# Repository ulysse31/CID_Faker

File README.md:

# DISCLAIMER :
# THIS PROJECT IS A PATCH MADE BY MYSELF, FOR MYSELF, AND IT AIMS TO COMPENSATE, THE LACK OF BUG CORRECTIONS IN THIRD PARTY REPLACEMENT SCREENS (CHINESE ANDROID BASED SCREENS) THAT DO NOT HAVE IMPLEMENTED THIS PARTICULAR CASE ON THEIR MCU FIRMWARE...

# WARNING !!! WE ARE TALKING ABOUT INJECTING DATA TO THE CAR NETWORK, THIS IS AT YOUR OWN RISK !!! I WILL NOT BE RESPONSIBLE FOR ANY HARM YOU MAY CAUSE TO YOUR CAR, YOURSELF, OR ANY OTHER
# YOU HAVE BEEN WARNED !!!
# CID_Faker
A CID can bus simulator:

CID (Central Information Display) on BMW cars from 2004 to 2011 is the designation for the car LCD screen.
Some of those screens are connected to the can bus of the car (at least BMW flap screens).
If you try to replace this type of screen with something else (like an Android Head Unit) you'll loose the ability to 
interact with the BMW original menu (no actions from idrive interpreted).

This project supposes that this is because of the absence of the can message id from the screen : "why take into
account moves from idrive if no screen detected" ... thats what the engineer may have thought when implementing this
on the CCC controller ...

This little code will so generate fake CID id messages on the can bus of the car, to simulate the presence of the CID.
CID sends messages with id 0x33a (status) and 0x4f3 (network).
All the main job will be to find the right messages, their combinations and timings.

Project uses platformIO for easy compilation and development.

For now, I'm using a Pro Micro board 5V@16Mhz, and a well known MCP2515 CAN Controller module, more precisely the
MCP2515 CAN controller with a 8Mhz oscillator and TJA1050 CAN transceiver.

You'll find on "Hardware" folder 2 types of designs :

- USB_Powered (tested working/recommended): this light version aims to be connected to the Android HU on its USB port, allowing it to be
powered up once the Android is up (key car inserted), and powered off when Android goes off (key car taken out)

- Standalone (not tested/under construction): this version aims to be more "unrelated" the Android HU, it is up the user to find a power
cable source from the car (preferrably, a source that is NOT always on ...)

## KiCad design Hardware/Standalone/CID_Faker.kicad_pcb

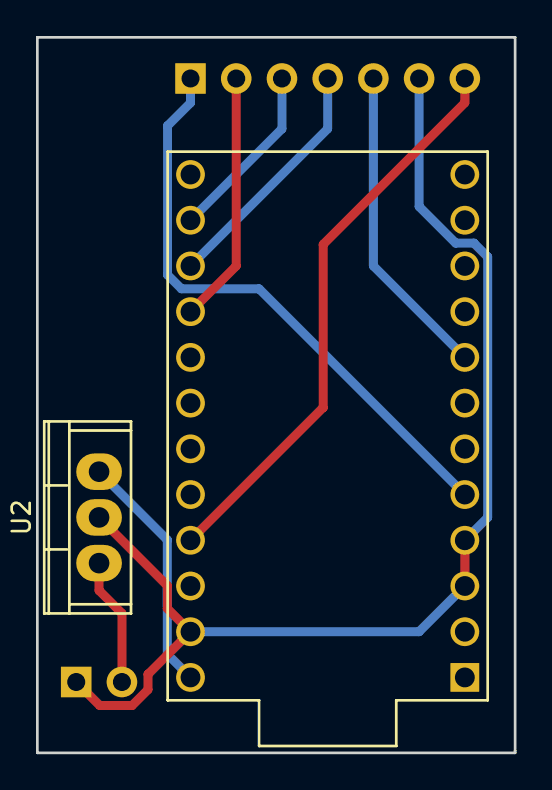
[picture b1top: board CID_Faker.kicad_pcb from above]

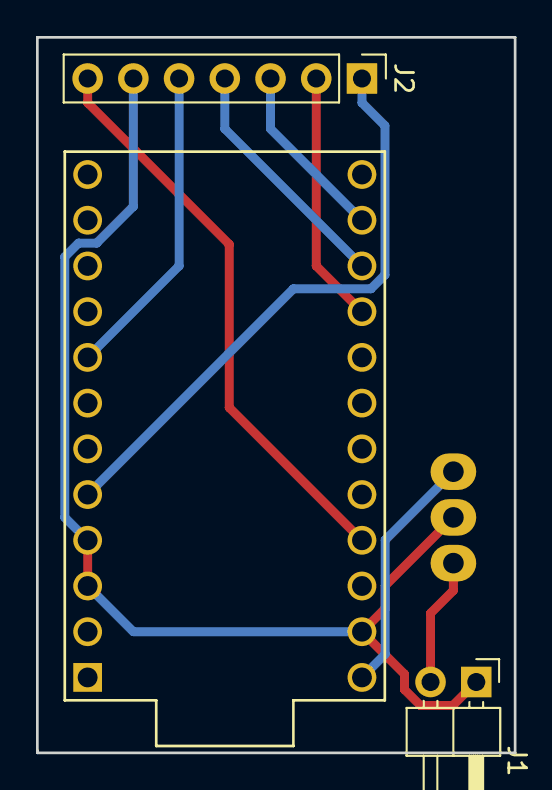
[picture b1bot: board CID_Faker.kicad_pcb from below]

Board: 2 copper layers, 26.5 x 39.8 mm, 4 parts (2 on the bottom side), 9 nets.

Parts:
J1: PWR; Pin_Header_Angled_1x02_Pitch2.54mm
J2: CAN; Socket_Strip_Straight_1x07_Pitch2.54mm
U1: ProMicro
U2: LF80_TO220; TO-220

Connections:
CS: J2.5, U1.8
GND: J1.1, J2.6, U1.3, U1.4, U1.23, U2.2
INT: J2.1, U1.5
MISO: J2.4, U1.15
MOSI: J2.3, U1.14
RAW: U1.24, U2.3
SCK: J2.2, U1.16
VCC: J2.7, U1.21
VIN: J1.2, U2.1

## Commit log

2019-05-31 first try
2019-05-31 added documentation on BMW CAN IDs listing. added can data logs from car with and without CID.
2019-05-31 set MCP freq of received modules
2019-06-01 final main with first lib
2019-06-01 changed to other mcp2515 lib seems old one does not work correctly on 8Mhz MCP @100kbps
2019-06-01 corrected "visual" bug on error signaling
2019-06-01 removed old lib commented code
2019-06-01 cleanup code
2019-06-01 added some project description
2019-06-02 - changed timeout in can lib : from 50 to 100 : 50 not adapted to 100kbps@8Mhz - changed main table send loop to do retries if not sent correctly - TESTED WORKING :D
2019-06-05 added README for library
2019-06-05 updated lib description
2019-06-05 removed useless readme in lib root
2019-06-05 updated project description
2019-06-05 updated description
2019-06-05 readme update again
2019-06-05 created 2 hardware profiles :
    - USB Powered : will contain a light version, that will use a usb port from android
    if android boots (ignition) it will automatically boot
    if android stops (car key off) it will automatically turn off the arduino
    - Standalone : a "standalone" version, allowing to have it "distant" from the android HU
    it will be up to the user to find a power cable were to connect it (RAW battery or other)
2019-06-05 updated readme again
2019-06-05 updated readme ...
2019-06-05 update readme ...
2019-06-06 not compilling !! WIP : restructuring sending code
2019-06-06 restructured sending code to met requirements for different send cycles between 0x33a and 0x4f3. NOT YET TESTED ^^' TBD
2019-06-06 optimized a bit the code, STILL NOT YET TESTED ^^'
2019-06-07 cleared a bit the code corrected aesthetical bug on activity led ...
2019-06-07 updated disclaimer added more precision to timing values (calculated from dump)
2019-06-07 removed warning compilation (unused variable ...)
2019-06-07 Had more time to really code at last one hour of coding and debugging: - corrected a dirty error on conditions - removed useless tests, variables and piece of code by changing a bit the algorithm - o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
    ... what else ?! :p
2019-06-07 Corrected a "potential" bug : if for some reason, it could not send packets during a given period of time it would send them all in one when connection would be established again if for some reason i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
2019-06-07 code optimization: - "useless double condition" removal ^^
2019-06-07 code optimization again ...
2019-06-07 removed commented debug values
2019-06-07 added GPL3 header to this tiny code ...
2019-06-07 Updated USB powered version schematics
2019-06-08 Corrected timing error at init in algorithm
2019-06-09 added explanations and instructions for possible future adaptation
2019-06-09 corrected some comments
2019-06-14 upgraded to kicad 5 updated schematics and PCB
2019-06-14 added license.md
2019-06-14 updated license
2019-06-15 Updated schema : longer but smaller ^^' (possibility to solder arduino and mcp module directly without header connectors)
2019-06-17 Update main.cpp
    removed "ugly" semantic error ^^'
2019-07-18 added a PDF view of the usbpowered schematic for simpler pinout connection view
